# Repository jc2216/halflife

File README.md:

## Starbie
A tiny motion-controlled digital pet, built for HackClub Halflife because I really want a 3D printer.
New Things!!! I added a buzzer so that twinkle twinkle little star plays when the sprite is napping. I also added a rain animation when the humidity>certain amt. We'll see if that works. 

Next Steps: 
* Change up some of the animations.
* implement sound during other actions/when using the selection thing.

---

## Process
1. Designed the Schematic

2. PCB routing and created a funny shape with it

3. Firmware! Added sparkles and created own sprite

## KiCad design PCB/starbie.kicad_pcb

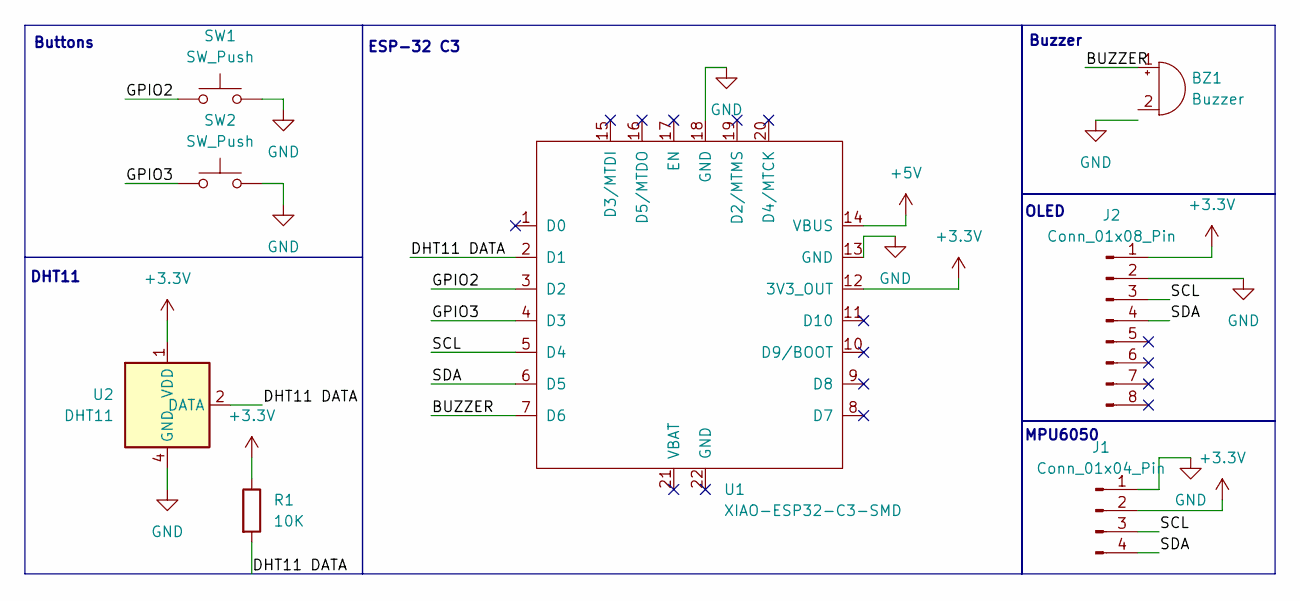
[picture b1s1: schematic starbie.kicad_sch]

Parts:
BZ1: Buzzer; Buzzer_TDK_PS1240P02BT_D12.2mm_H6.5mm
J1: Conn_01x04_Pin; Display_128x64_096_I2C
J2: Conn_01x08_Pin; PinHeader_1x08_P2.54mm_Vertical
R1: 10K; R_Axial_DIN0204_L3.6mm_D1.6mm_P7.62mm_Horizontal
SW1, SW2: SW_Push; SW_Cherry_MX_1.00u_PCB
U1: XIAO-ESP32-C3-SMD
U2: DHT11; Aosong_DHT11_5.5x12.0_P2.54mm

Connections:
+3.3V: J1.2, J2.1, R1.1, U1.12 (3V3_OUT), U2.1 (VDD)
+5V: U1.14 (VBUS)
/BUZZER: BZ1.1 (+_1), U1.7 (D6)
/DHT11 DATA: R1.2, U1.2 (D1), U2.2 (DATA)
/GPIO2: SW1.1, U1.3 (D2)
/GPIO3: SW2.1, U1.4 (D3)
/SCL: J1.3, J2.3, U1.5 (D4)
/SDA: J1.4, J2.4, U1.6 (D5)
GND: J1.1, J2.2, SW1.2, SW2.2, U1.13 (GND), U1.18 (GND), U2.4 (GND)

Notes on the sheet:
ESP-32 C3
DHT11
OLED
MPU6050
Buttons
Buzzer

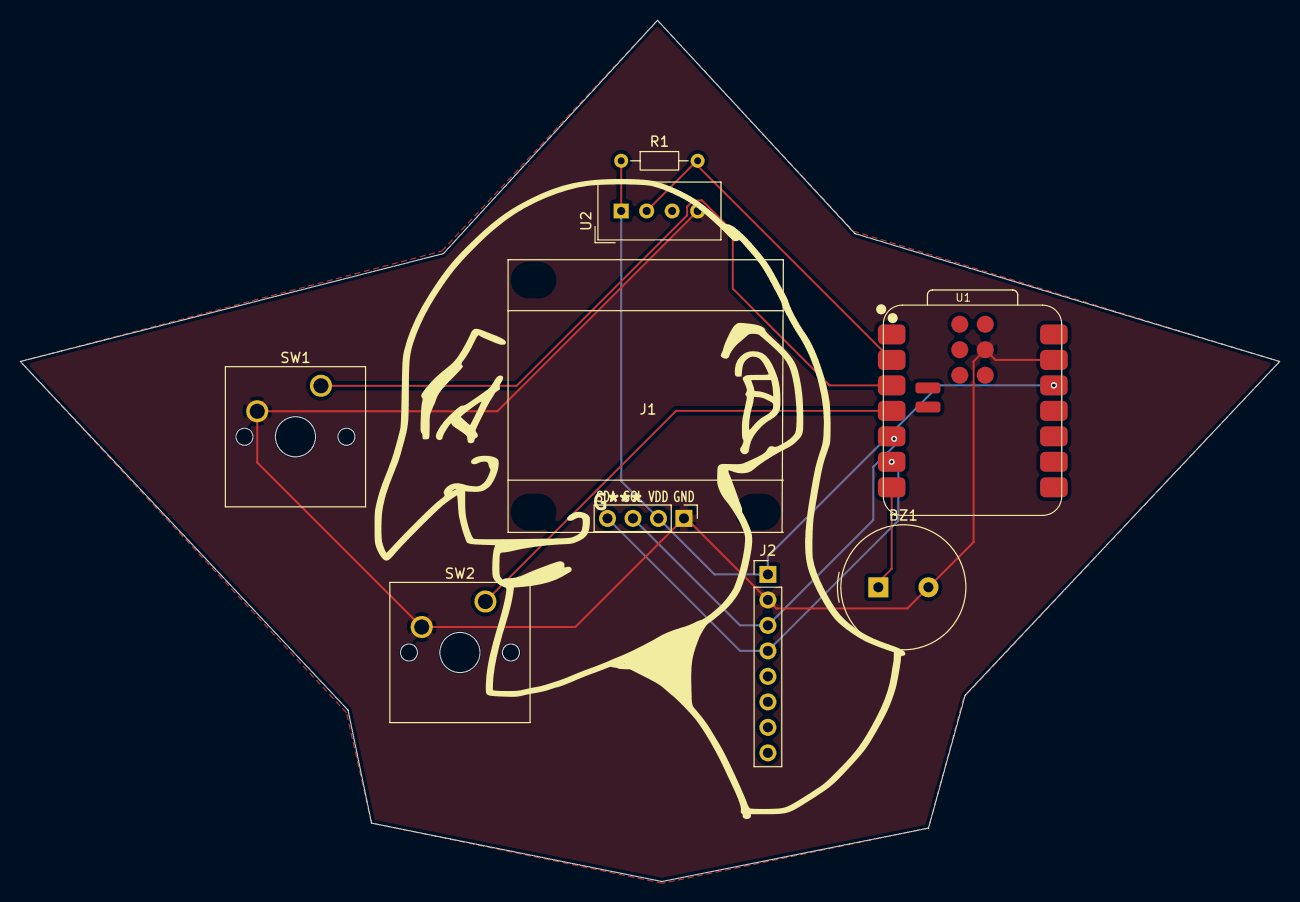
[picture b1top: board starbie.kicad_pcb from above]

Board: 2 copper layers, 125.5 x 85.8 mm, 8 parts (0 on the bottom side), 8 nets.
